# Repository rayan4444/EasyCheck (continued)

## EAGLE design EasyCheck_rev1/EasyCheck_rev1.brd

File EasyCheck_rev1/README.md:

# EasyCheck rev1

This first revision is meant for a purely test basis.
As there are many hardware bugs on this version, the code is just a collection of functions meant to be modified to test a specific feature independently; in preparation for a better version 2 board.

## Hardware Connections
(arduino PIN), Chip Pin: functionality

###### Programming:
- (44) PA30: SWCLK
- (45) PA31: SWDIO
- (28) PA24: USBD_N
- (29) PA25: USBD_P
- NRESET: nRESET

###### Chip Status:
- (26) PA27: Chip 7 status
- (31) PB23: Chip 6 status
- (8) PA06: Chip 5 status
- (9) PA07: Chip 4 status
- (1) PA10: Chip 3 status
- (0) PA11: Chip 2 status
- (2) PA14: Chip 1 status
- (5) PA15: Chip 0 status

###### Chip Serial Number:
- (6) PA20: Serial number 1W

###### User Input:
- (19) PB02: Button 1
- (25) PB03: Button2

###### External ADCs (resistance and chip temperature data):
- (20) PA22 SERCOM 3+5.0: SDA1
- (21) PA23 SERCOM3+5.1: SCL1

###### I2C OLED DISPLAY
- (22) PA12 SERCOM2+4.0: SDA2
- (28) PA13 SERCOM2+4.1: SCL2

###### External DAC (power supply TEC controllers):
- (4) PA08 SERCOM0 + 2.0: SDA3
- (3) PA09 SERCOM 0+ 2.1: SCL3
- (17) PA04: LDAC
- (18) PA05: TEC_EN

###### SPI SD CARD:
- (11) PA16 SERCOM1.0: MOSI
- (13) PA17 SERCOM1.1: SCK
- (10) PA18 SERCOM1.2: /SS
- (12) PA19 SERCOM1.3: MISO
- (30) PB22: Card Detect

###### Device Temperature:
- (7) PA21: 1W Temperature

###### Motor driver TEC input Or Alternative power supply TEC input:
- (15) PB08: PWM0
- (16) PB09: PWM1

###### Alternative power supply TEC input:
- (23) PB10: PWM2
- (24) PB11: PWM3

###### Internal DAC：
- PA02: DAC

## Hardware Errata and fixes

###### Power rail
- 12V to 5V switching regulator: changed from minimum ripple configuration (not working) to minimum cost configuration (see LM5085 datasheet). Still having issues with it output not smooth enough.
- Forgot to connect USB power line to the 5V rail

###### Signals
- I2C1: looks OK
- I2C2: rounded waveform but still functional
- I2C3: does not work. Still uncertain why.
- PWM 2&3 cannot be used with Arduino bootloader
- change 1W resistor to 1.5k for serial number reading
- SD card: remove CS pin pullup

###### Conceptual Errors
- For next version: remove chip status
- Connect every chip serial number to a different pin
- Change I2S screen to SPI screen
- Use Adalogger M0 design for SD card connection
- Change TEC to resistive heater: new driver

## References and Tutorials
###### Programming using OpenOCD and a Raspberry Pi:
- https://learn.adafruit.com/programming-microcontrollers-using-openocd-on-raspberry-pi/overview

###### Assigning SERCOM on SAMD21G:
- https://learn.adafruit.com/using-atsamd21-sercom-to-add-more-spi-i2c-serial-ports/overview

###### Logging data on SD card using RTC for timestamps
- https://github.com/cavemoa/Feather-M0-Adalogger/blob/master/LowPowerLogger/LowPowerLogger.ino

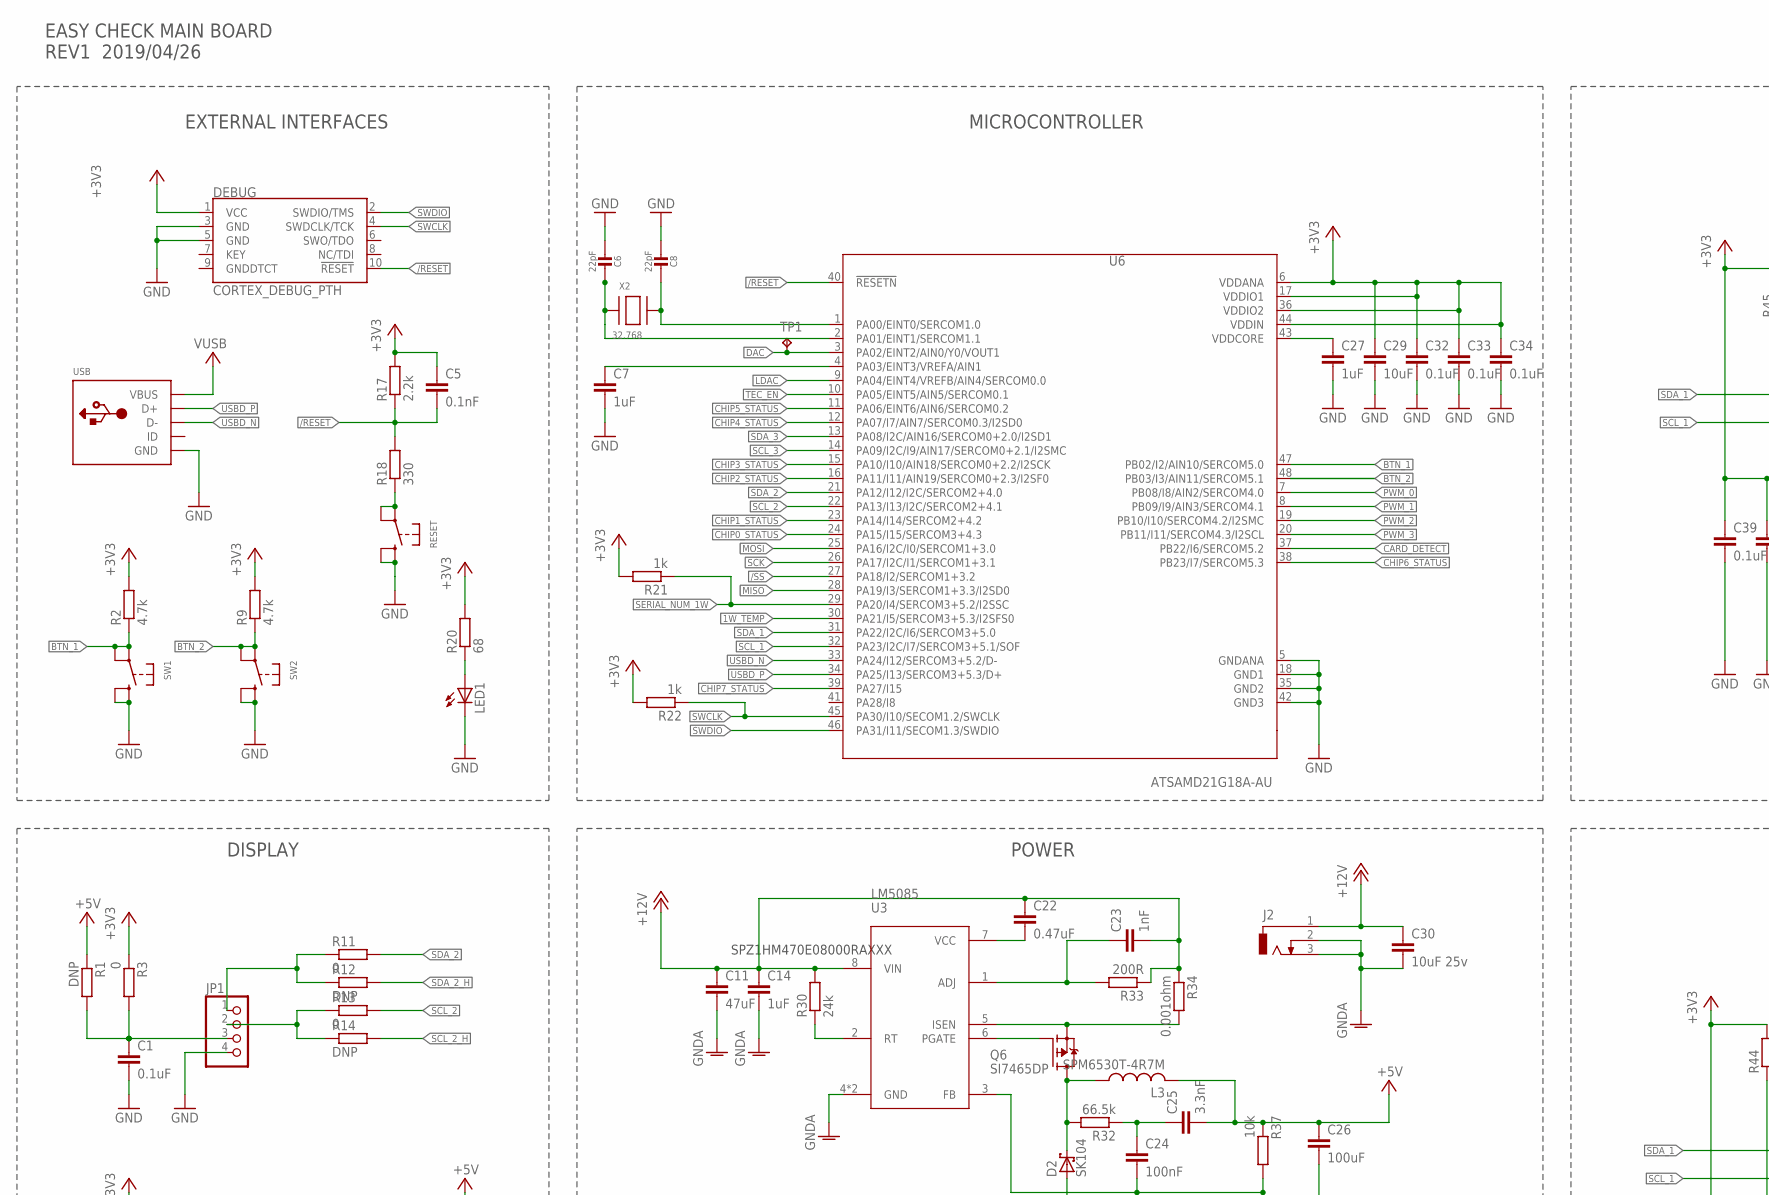
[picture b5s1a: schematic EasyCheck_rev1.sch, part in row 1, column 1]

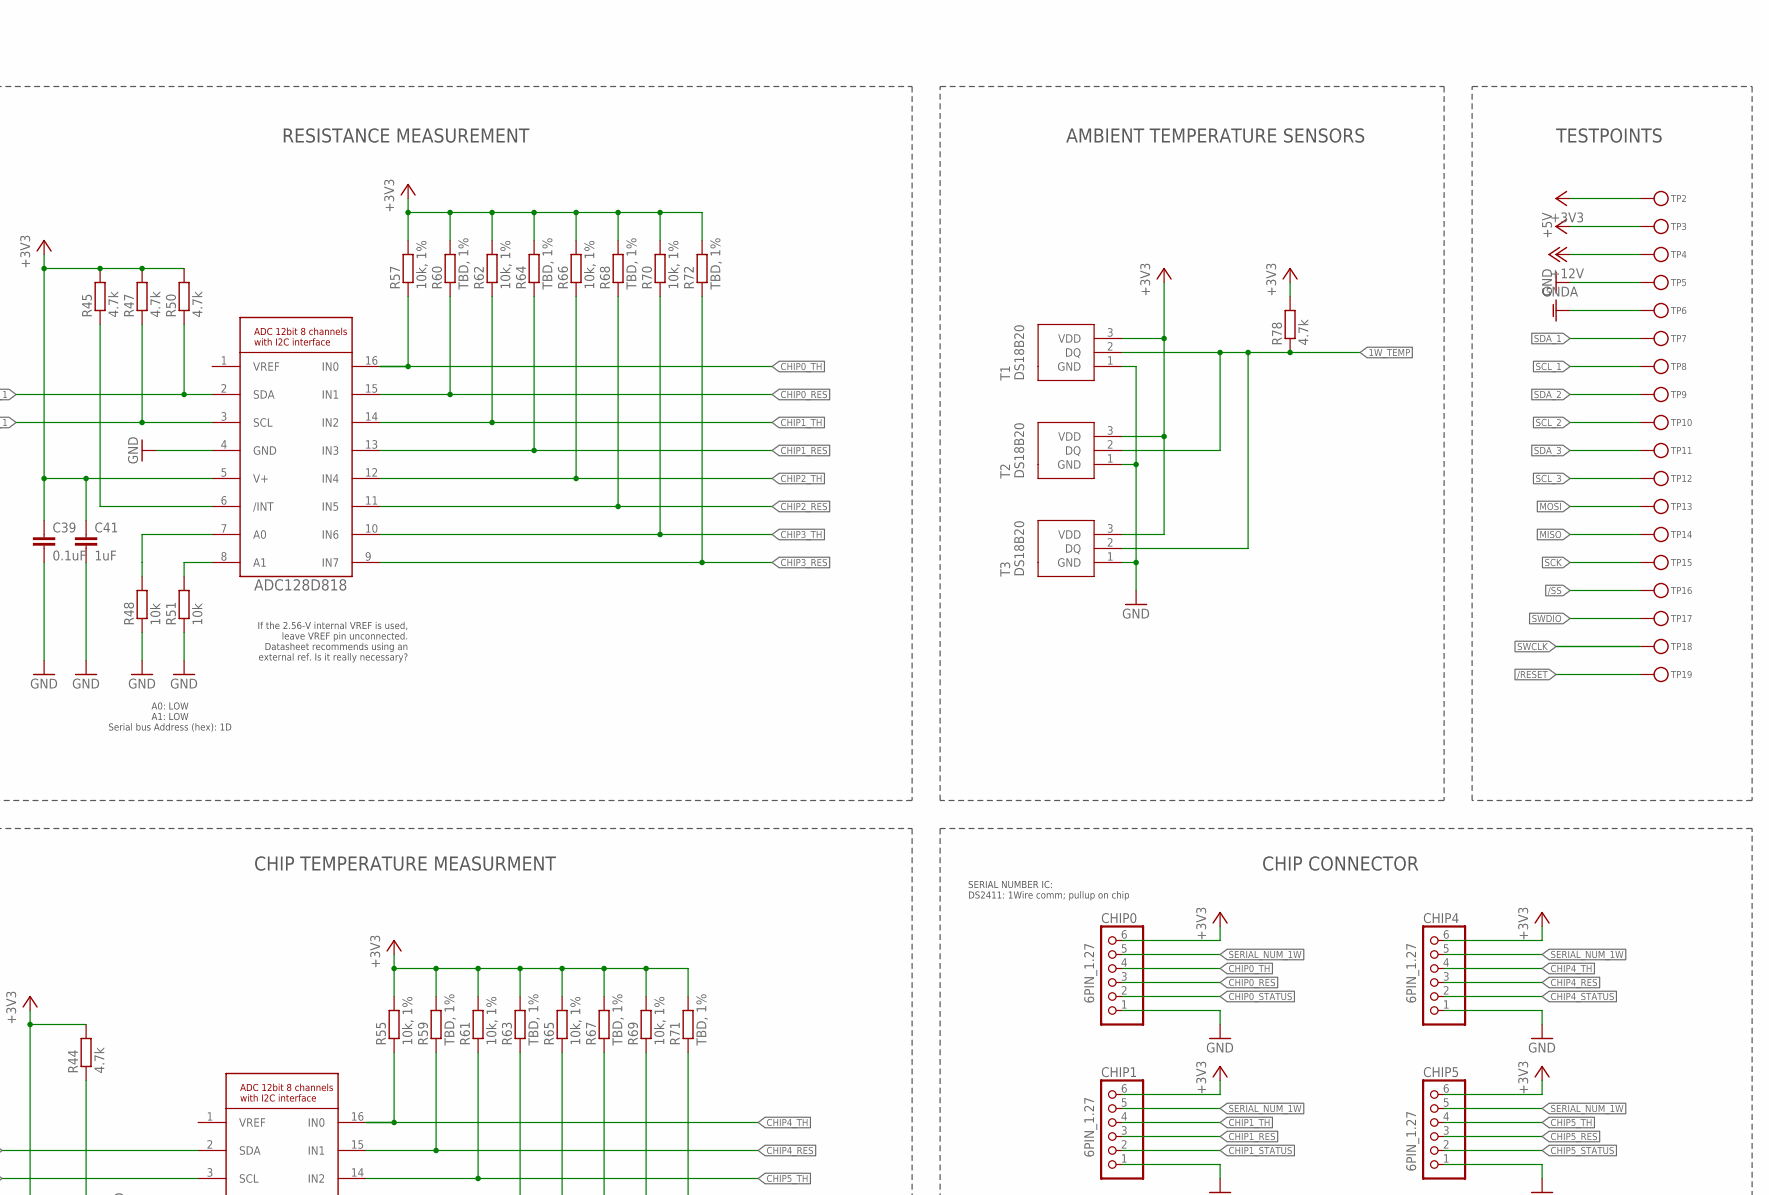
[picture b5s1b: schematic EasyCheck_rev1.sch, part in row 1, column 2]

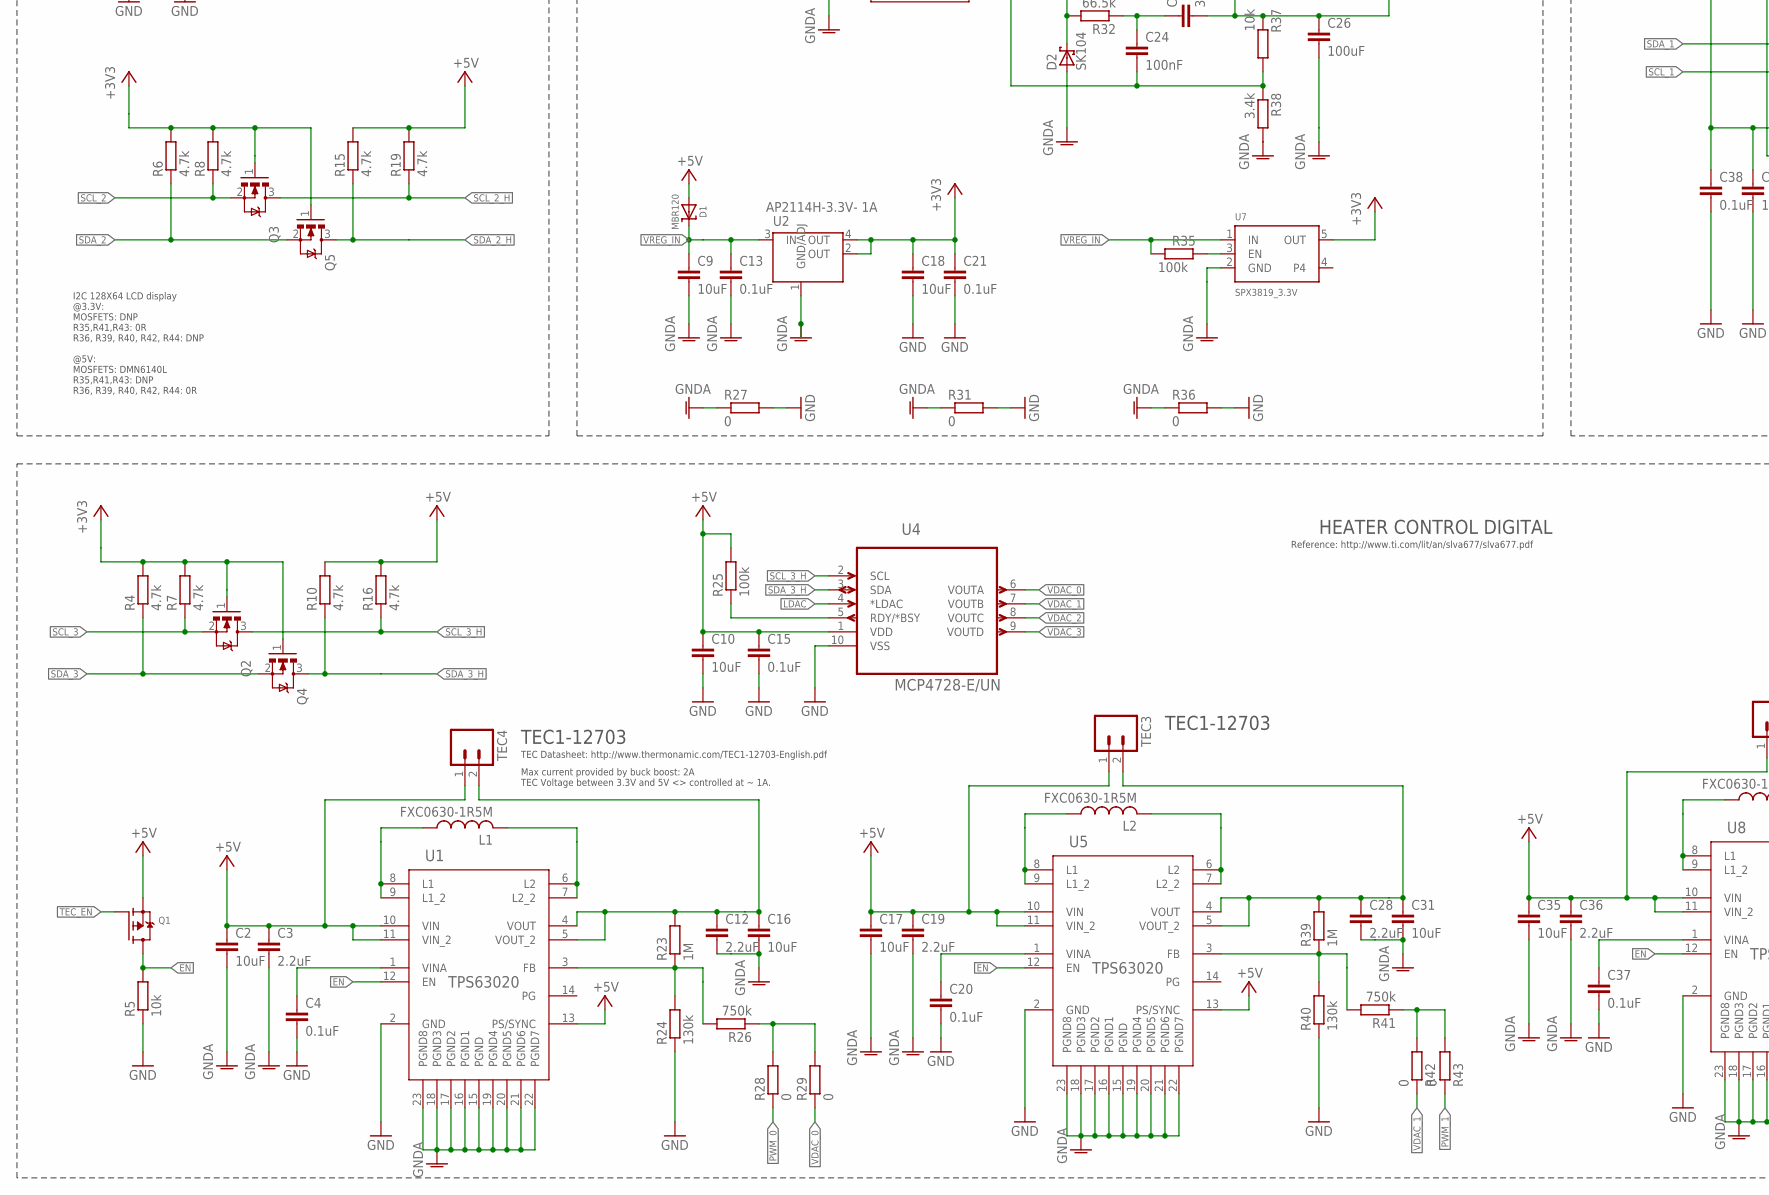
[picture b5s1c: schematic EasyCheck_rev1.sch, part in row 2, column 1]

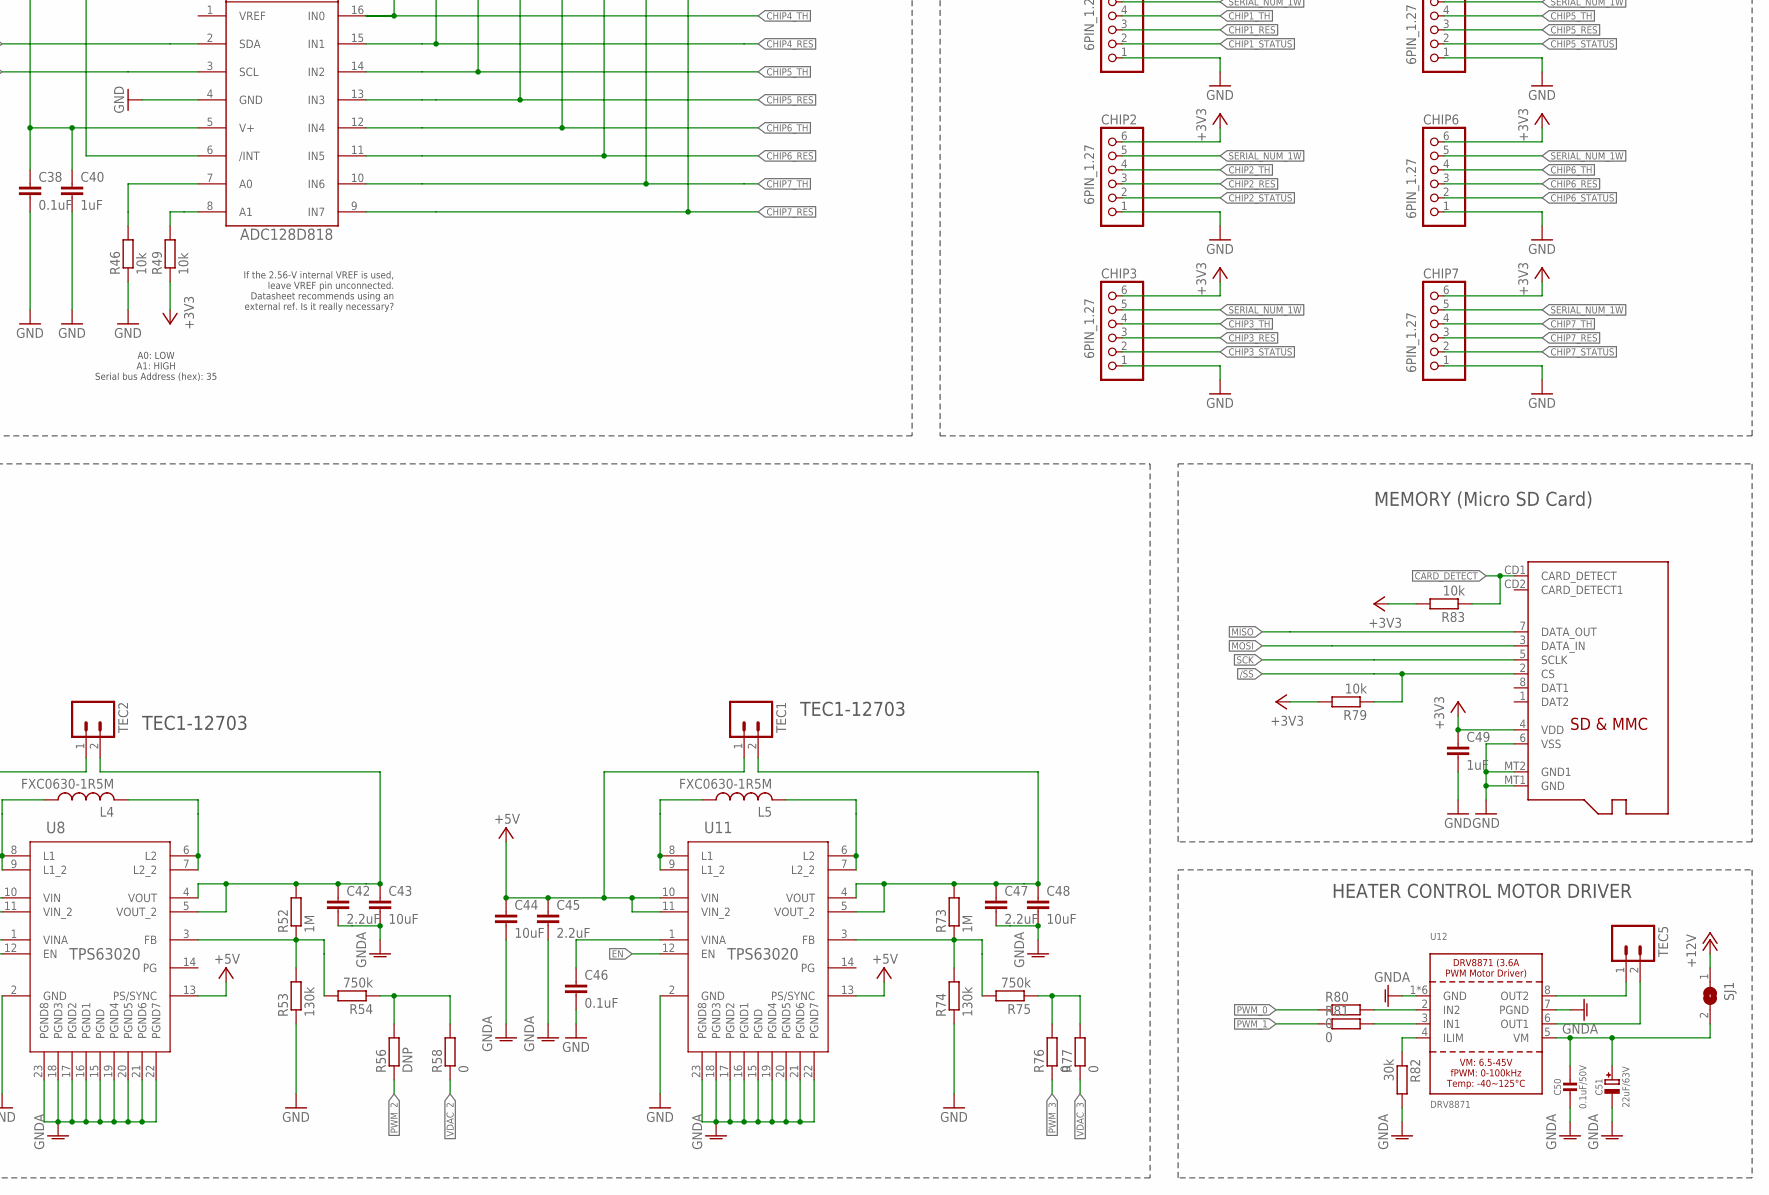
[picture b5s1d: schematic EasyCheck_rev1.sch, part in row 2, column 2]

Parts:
C1, C4, C13, C15, C20, C21, C32, C33, C34, C37, C38, C39, C46: 0.1uF; C0603
C2, C16, C17, C31, C43, C44, C48: 10uF; C0805
C3, C12, C19, C28, C42, C45, C47: 2.2uF; C0805
C5: 0.1nF; C0603
C6, C8: 22pF; 0603-NO
C7, C27, C40, C41, C49: 1uF; C0603
C9, C10, C18, C29, C35: 10uF; C0603
C11: 47uF; C1206
C14: 1uF; C1206
C22: 0.47uF; C1206
C23: 1nF; C0603
C24: 100nF; C0603
C25: 3.3nF; C0603
C26: 100uF; C1206
C30: 10uF 25v; C1206
C36: 2.2uF; C0603
C50: 0.1uF/50V; 0805-NO
C51: 22uF/63V; PANASONIC_D
CHIP0, CHIP1, CHIP2, CHIP3, CHIP4, CHIP5, CHIP6, CHIP7: 6PIN_1.27; 6X1PIN_1.27
D1: MBR120; MICROBUILDER_SOD-123
D2: SK104
DEBUG: CORTEX_DEBUG_PTH; 2X5-PTH-1.27MM
J2: DCJ0303
JP1: PINHD-1X4; 1X04
L1, L2, L4, L5: FXC0630-1R5M; PIS2816
L3: SPM6530T-4R7M
LED1: LEDCHIPLED_0603; CHIPLED_0603
Q1: MICROBUILDER_MOSFET-P; MICROBUILDER_SOT23-R
Q2, Q3, Q4, Q5: DMN6140L; SOT91P240X110-3N
Q6: SI7465DP; SI7465
R1, R12, R14, R56: DNP; R0603
R2, R4, R6, R7, R8, R9, R10, R15, R16, R19, R44, R45, R47, R50, R78: 4.7k; R0603
R3, R11, R13, R27, R28, R29, R31, R36, R42, R43, R58, R76, R77, R80, R81: 0; R0603
R5, R37, R46, R48, R49, R51, R79, R83: 10k; R0603
R17: 2.2k; R0603
R18: 330; R0603
R20: 68; R0603
R21, R22: 1k; R0603
R23, R39, R52, R73: 1M; R0603
R24, R40, R53, R74: 130k; R0603
R25, R35: 100k; R0603
R26, R41, R54, R75: 750k; R0603
R30: 24k; R0603
R32: 66.5k; R0603
R33: 200R; R0603
R34: 0.001ohm; R1206
R38: 3.4k; R0603
R55, R57, R61, R62, R65, R66, R69, R70: 10k, 1%; R0603
R59, R60, R63, R64, R67, R68, R71, R72: TBD, 1%; R0603
R82: 30k; R0603
RESET: MICROBUILDER_SWITCH_TACT_SMT_EVQQ2_SMALL; MICROBUILDER_EVQ-Q2_SMALLER
SD1: MICROSD
SJ1: SJW
SW1, SW2: MICROBUILDER_SWITCH_TACT_SMT_EVQQ2_SMALL; MICROBUILDER_EVQ-Q2_SMALLER
T1, T2, T3: DS18B20; TO92
TEC1, TEC2, TEC3, TEC4, TEC5: SPARKFUN-CONNECTORS_M025MM; SPARKFUN-CONNECTORS_SCREWTERMINAL-5MM-2$1
TP1: TPPAD1-17; P1-17
TP2, TP3, TP4, TP5, TP6, TP7, TP8, TP9, TP10, TP11, TP12, TP13, TP14, TP15, TP16, TP17, TP18, TP19: MICROBUILDER_TESTPOINTROUND1.5MM; MICROBUILDER_TESTPOINT_ROUND_1.5MM
U1, U5, U8, U11: TPS63020; QFN14-3X4MM
U2: AP2114H-3.3V- 1A; GEN_COMP_SOT223
U3: LM5085
U4: MCP4728-E/UN; SOP50P490X110-10N
U6: ATSAMD21G18A-AU; QFP50P900X900X120-48N
U7: SPX3819_3.3V; MICROBUILDER_SOT23-5
U9, U10: LMD128D818; ADC128D818
U12: DRV8871; HSOP8
USB: MICROBUILDER_USB_MICRO_20329_V2; MICROBUILDER_4UCONN_20329_V2
X2: 32.768; XTAL3215

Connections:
1W_TEMP: R78.1, T1.2 (DQ), T2.2 (DQ), T3.2 (DQ), U6.30 (PA21/I5/SERCOM3+5.3/I2SFS0)
+3V3: C5.1, C18.1, C21.1, C29.1, C32.1, C33.1, C34.1, C38.1, C39.1, C40.1, C41.1, C49.1, CHIP0.6, CHIP1.6, CHIP2.6, CHIP3.6, CHIP4.6, CHIP5.6, CHIP6.6, CHIP7.6, DEBUG.1 (VCC), Q2.1, Q3.1, Q4.1, Q5.1, R2.2, R3.1, R4.2, R6.2, R7.2, R8.2, R9.2, R17.2, R20.2, R21.2, R22.2, R44.2, R45.2, R47.2, R49.1, R50.2, R55.2, R57.2, R59.2, R60.2, R61.2, R62.2, R63.2, R64.2, R65.2, R66.2, R67.2, R68.2, R69.2, R70.2, R71.2, R72.2, R78.2, R79.2, R83.2, SD1.4 (VDD), T1.3 (VDD), T2.3 (VDD), T3.3 (VDD), TP2.P$1, U2.2 (OUT), U2.4 (OUT), U6.6 (VDDANA), U6.17 (VDDIO1), U6.36 (VDDIO2), U6.44 (VDDIN), U7.5 (OUT), U9.5 (V+), U10.5 (V+)
+5V: C2.1, C3.1, C10.1, C15.1, C17.1, C19.1, C25.2, C26.1, C35.1, C36.1, C44.1, C45.1, D1.A, L3.2, Q1.2 (S), R1.1, R10.2, R15.2, R16.2, R19.2, R25.2, R37.1, TEC1.1, TEC2.1, TEC3.1, TEC4.1, TP3.P$1, U1.10 (VIN), U1.11 (VIN_2), U1.13 (PS/SYNC), U4.1 (VDD), U5.10 (VIN), U5.11 (VIN_2), U5.13 (PS/SYNC), U8.10 (VIN), U8.11 (VIN_2), U8.13 (PS/SYNC), U11.10 (VIN), U11.11 (VIN_2), U11.13 (PS/SYNC)
+12V: C11.1, C14.1, C22.1, C23.2, C30.1, J2.1, R30.2, R33.1, R34.1, SJ1.1, TP4.P$1, U3.8 (VIN)
/RESET: C5.2, DEBUG.10 (!RESET), R17.1, R18.2, TP19.P$1, U6.40 (!RESETN)
/SS: R79.1, SD1.2 (CS), TP16.P$1, U6.27 (PA18/I2/SERCOM1+3.2)
BTN_1: R2.1, SW1.A, SW1.A' (P1), U6.47 (PB02/I2/AIN10/SERCOM5.0)
BTN_2: R9.1, SW2.A, SW2.A' (P1), U6.48 (PB03/I3/AIN11/SERCOM5.1)
CARD_DETECT: R83.1, SD1.CD1 (CARD_DETECT), U6.37 (PB22/I6/SERCOM5.2)
CHIP0_RES: CHIP0.3, R60.1, U10.15 (IN1)
CHIP0_STATUS: CHIP0.2, U6.24 (PA15/I15/SERCOM3+4.3)
CHIP0_TH: CHIP0.4, R57.1, U10.16 (IN0)
CHIP1_RES: CHIP1.3, R64.1, U10.13 (IN3)
CHIP1_STATUS: CHIP1.2, U6.23 (PA14/I14/SERCOM2+4.2)
CHIP1_TH: CHIP1.4, R62.1, U10.14 (IN2)
CHIP2_RES: CHIP2.3, R68.1, U10.11 (IN5)
CHIP2_STATUS: CHIP2.2, U6.16 (PA11/I11/AIN19/SERCOM0+2.3/I2SF0)
CHIP2_TH: CHIP2.4, R66.1, U10.12 (IN4)
CHIP3_RES: CHIP3.3, R72.1, U10.9 (IN7)
CHIP3_STATUS: CHIP3.2, U6.15 (PA10/I10/AIN18/SERCOM0+2.2/I2SCK)
CHIP3_TH: CHIP3.4, R70.1, U10.10 (IN6)
CHIP4_RES: CHIP4.3, R59.1, U9.15 (IN1)
CHIP4_STATUS: CHIP4.2, U6.12 (PA07/I7/AIN7/SERCOM0.3/I2SD0)
CHIP4_TH: CHIP4.4, R55.1, U9.16 (IN0)
CHIP5_RES: CHIP5.3, R63.1, U9.13 (IN3)
CHIP5_STATUS: CHIP5.2, U6.11 (PA06/EINT6/AIN6/SERCOM0.2)
CHIP5_TH: CHIP5.4, R61.1, U9.14 (IN2)
CHIP6_RES: CHIP6.3, R67.1, U9.11 (IN5)
CHIP6_STATUS: CHIP6.2, U6.38 (PB23/I7/SERCOM5.3)
CHIP6_TH: CHIP6.4, R65.1, U9.12 (IN4)
CHIP7_RES: CHIP7.3, R71.1, U9.9 (IN7)
CHIP7_STATUS: CHIP7.2, U6.39 (PA27/I15)
CHIP7_TH: CHIP7.4, R69.1, U9.10 (IN6)
DAC: TP1.TP, U6.3 (PA02/EINT2/AIN0/Y0/VOUT1)
EN: Q1.3 (D), R5.2, U1.12 (EN), U5.12 (EN), U8.12 (EN), U11.12 (EN)
GND: C1.2, C4.2, C6.2, C7.2, C8.2, C10.2, C15.2, C18.2, C20.2, C21.2, C27.2, C29.2, C32.2, C33.2, C34.2, C37.2, C38.2, C39.2, C40.2, C41.2, C46.2, C49.2, CHIP0.1, CHIP1.1, CHIP2.1, CHIP3.1, CHIP4.1, CHIP5.1, CHIP6.1, CHIP7.1, DEBUG.3 (GND), DEBUG.5 (GND), JP1.4, LED1.C, R5.1, R24.1, R27.2, R31.2, R36.2, R40.1, R46.1, R48.1, R51.1, R53.1, R74.1, RESET.B (S), RESET.B' (S1), SD1.6 (VSS), SD1.MT1 (GND), SD1.MT2 (GND1), SW1.B (S), SW1.B' (S1), SW2.B (S), SW2.B' (S1), T1.1 (GND), T2.1 (GND), T3.1 (GND), TP5.P$1, U1.2 (GND), U4.10 (VSS), U5.2 (GND), U6.5 (GNDANA), U6.18 (GND1), U6.35 (GND2), U6.42 (GND3), U8.2 (GND), U9.4 (GND), U10.4 (GND), U11.2 (GND), USB.BASE@1 (GND), USB.BASE@2 (GND), USB.GND, USB.SPRT@1 (GND), USB.SPRT@2 (GND), USB.SPRT@3 (GND), USB.SPRT@4 (GND)
GNDA: C2.2, C3.2, C9.2, C11.2, C12.2, C13.2, C14.2, C16.2, C17.2, C19.2, C26.2, C28.2, C30.2, C31.2, C35.2, C36.2, C42.2, C43.2, C44.2, C45.2, C47.2, C48.2, C50.2, C51.-, D2.1 (A), J2.2, J2.3, R27.1, R31.1, R36.1, R38.2, R82.2, TP6.P$1, U1.15 (PGND), U1.16 (PGND1), U1.17 (PGND2), U1.18 (PGND3), U1.19 (PGND4), U1.20 (PGND5), U1.21 (PGND6), U1.22 (PGND7), U1.23 (PGND8), U2.1 (GND/ADJ), U3.4 (GND), U3.9 (GND), U5.15 (PGND), U5.16 (PGND1), U5.17 (PGND2), U5.18 (PGND3), U5.19 (PGND4), U5.20 (PGND5), U5.21 (PGND6), U5.22 (PGND7), U5.23 (PGND8), U7.2 (GND), U8.15 (PGND), U8.16 (PGND1), U8.17 (PGND2), U8.18 (PGND3), U8.19 (PGND4), U8.20 (PGND5), U8.21 (PGND6), U8.22 (PGND7), U8.23 (PGND8), U11.15 (PGND), U11.16 (PGND1), U11.17 (PGND2), U11.18 (PGND3), U11.19 (PGND4), U11.20 (PGND5), U11.21 (PGND6), U11.22 (PGND7), U11.23 (PGND8), U12.1 (GND), U12.7 (PGND), U12.GND, U12.P$1 (GND), U12.P$2 (GND), U12.P$3 (GND), U12.P$4 (GND)
LDAC: U4.4 (*LDAC), U6.9 (PA04/EINT4/VREFB/AIN4/SERCOM0.0)
MISO: SD1.7 (DATA_OUT), TP14.P$1, U6.28 (PA19/I3/SERCOM1+3.3/I2SD0)
MOSI: SD1.3 (DATA_IN), TP13.P$1, U6.25 (PA16/I2C/I0/SERCOM1+3.0)
unnamed: R45.1, U10.6 (/INT)
unnamed: R44.1, U9.6 (/INT)
unnamed: R48.2, U10.7 (A0)
unnamed: R51.2, U10.8 (A1)
unnamed: R46.2, U9.7 (A0)
unnamed: R49.2, U9.8 (A1)
unnamed: R18.1, RESET.A, RESET.A' (P1)
unnamed: R35.2, U7.3 (EN)
unnamed: JP1.1, R11.1, R12.1
unnamed: C6.1, U6.2 (PA01/EINT1/SERCOM1.1), X2.P$1
unnamed: C8.1, U6.1 (PA00/EINT0/SERCOM1.0), X2.P$2
unnamed: C7.1, U6.4 (PA03/EINT3/VREFA/AIN1)
unnamed: C27.1, U6.43 (VDDCORE)
unnamed: LED1.A, R20.1
unnamed: JP1.2, R13.1, R14.1
unnamed: R26.1, R28.2, R29.2
unnamed: R23.1, R24.2, R26.2, U1.3 (FB)
unnamed: C4.1, U1.1 (VINA)
unnamed: L1.1, U1.8 (L1), U1.9 (L1_2)
unnamed: C12.1, C16.1, R23.2, TEC4.2, U1.4 (VOUT), U1.5 (VOUT_2)
unnamed: L1.2, U1.6 (L2), U1.7 (L2_2)
unnamed: R41.1, R42.2, R43.2
unnamed: C20.1, U5.1 (VINA)
unnamed: R30.1, U3.2 (RT)
unnamed: R39.1, R40.2, R41.2, U5.3 (FB)
unnamed: C28.1, C31.1, R39.2, TEC3.2, U5.4 (VOUT), U5.5 (VOUT_2)
unnamed: L2.1, U5.8 (L1), U5.9 (L1_2)
unnamed: L2.2, U5.6 (L2), U5.7 (L2_2)
unnamed: R25.1, U4.5 (RDY/*BSY)
unnamed: R54.1, R56.2, R58.2
unnamed: C37.1, U8.1 (VINA)
unnamed: R52.1, R53.2, R54.2, U8.3 (FB)
unnamed: C42.1, C43.1, R52.2, TEC2.2, U8.4 (VOUT), U8.5 (VOUT_2)
unnamed: L4.1, U8.8 (L1), U8.9 (L1_2)
unnamed: L4.2, U8.6 (L2), U8.7 (L2_2)
unnamed: Q6.1 (S), Q6.2 (S), Q6.3 (S), R34.2, U3.5 (ISEN)
unnamed: R75.1, R76.2, R77.2
unnamed: C23.1, R33.2, U3.1 (ADJ)
unnamed: C24.1, C25.1, R32.1
unnamed: C24.2, R37.2, R38.1, U3.3 (FB)
unnamed: C46.1, U11.1 (VINA)
unnamed: R73.1, R74.2, R75.2, U11.3 (FB)
unnamed: C22.2, U3.7 (VCC)
unnamed: C47.1, C48.1, R73.2, TEC1.2, U11.4 (VOUT), U11.5 (VOUT_2)
unnamed: L5.1, U11.8 (L1), U11.9 (L1_2)
unnamed: L5.2, U11.6 (L2), U11.7 (L2_2)
unnamed: D2.2 (C), L3.1, Q6.5 (D), Q6.6 (D), Q6.7 (D), Q6.8 (D), Q6.9 (D), R32.2
unnamed: Q6.4 (G), U3.6 (PGATE)
unnamed: R82.1, U12.4 (ILIM)
unnamed: R80.2, U12.2 (IN2)
unnamed: R81.2, U12.3 (IN1)
unnamed: C50.1, C51.+, SJ1.2, U12.5 (VM)
OUT1: TEC5.2, U12.6 (OUT1)
OUT2: TEC5.1, U12.8 (OUT2)
PWM_0: R28.1, R80.1, U6.7 (PB08/I8/AIN2/SERCOM4.0)
PWM_1: R43.1, R81.1, U6.8 (PB09/I9/AIN3/SERCOM4.1)
PWM_2: R56.1, U6.19 (PB10/I10/SERCOM4.2/I2SMC)
PWM_3: R76.1, U6.20 (PB11/I11/SERCOM4.3/I2SCL)
SCK: SD1.5 (SCLK), TP15.P$1, U6.26 (PA17/I2C/I1/SERCOM1+3.1)
SCL_1: R47.1, TP8.P$1, U6.32 (PA23/I2C/I7/SERCOM3+5.1/SOF), U9.3 (SCL), U10.3 (SCL)
SCL_2: Q3.2, R8.1, R13.2, TP10.P$1, U6.22 (PA13/I13/I2C/SERCOM2+4.1)
SCL_2_H: Q3.3, R14.2, R19.1
SCL_3: Q2.2, R7.1, TP12.P$1, U6.14 (PA09/I2C/I9/AIN17/SERCOM0+2.1/I2SMC)
SCL_3_H: Q2.3, R16.1, U4.2 (SCL)
SDA_1: R50.1, TP7.P$1, U6.31 (PA22/I2C/I6/SERCOM3+5.0), U9.2 (SDA), U10.2 (SDA)
SDA_2: Q5.2, R6.1, R11.2, TP9.P$1, U6.21 (PA12/I12/I2C/SERCOM2+4.0)
SDA_2_H: Q5.3, R12.2, R15.1
SDA_3: Q4.2, R4.1, TP11.P$1, U6.13 (PA08/I2C/AIN16/SERCOM0+2.0/I2SD1)
SDA_3_H: Q4.3, R10.1, U4.3 (SDA)
SERIAL_NUM_1W: CHIP0.5, CHIP1.5, CHIP2.5, CHIP3.5, CHIP4.5, CHIP5.5, CHIP6.5, CHIP7.5, R21.1, U6.29 (PA20/I4/SERCOM3+5.2/I2SSC)
SWCLK: DEBUG.4 (SWDCLK/TCK), R22.1, TP18.P$1, U6.45 (PA30/I10/SECOM1.2/SWCLK)
SWDIO: DEBUG.2 (SWDIO/TMS), TP17.P$1, U6.46 (PA31/I11/SECOM1.3/SWDIO)
TEC_EN: Q1.1 (G), U6.10 (PA05/EINT5/AIN5/SERCOM0.1)
USBD_N: U6.33 (PA24/I12/SERCOM3+5.2/D-), USB.D-
USBD_P: U6.34 (PA25/I13/SERCOM3+5.3/D+), USB.D+
VCC: C1.1, JP1.3, R1.2, R3.2
VDAC_0: R29.1, U4.6 (VOUTA)
VDAC_1: R42.1, U4.7 (VOUTB)
VDAC_2: R58.1, U4.8 (VOUTC)
VDAC_3: R77.1, U4.9 (VOUTD)
VREG_IN: C9.1, C13.1, D1.C, R35.1, U2.3 (IN), U7.1 (IN)

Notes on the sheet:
EASY CHECK MAIN BOARD REV1 2019/04/26
CHIP CONNECTOR
DISPLAY
EXTERNAL INTERFACES
HEATER CONTROL DIGITAL
AMBIENT TEMPERATURE SENSORS
RESISTANCE MEASUREMENT
POWER
SERIAL NUMBER IC: DS2411: 1Wire comm; pullup on chip
CHIP TEMPERATURE MEASURMENT
If the 2.56-V internal VREF is used, leave VREF pin unconnected. Datasheet recommends using an external ref. Is it really necessary?
A0: LOW A1: LOW Serial bus Address (hex): 1D
A0: LOW A1: HIGH Serial bus Address (hex): 35
MICROCONTROLLER
I2C 128X64 LCD display @3.3V: MOSFETS: DNP R35,R41,R43: 0R R36, R39, R40, R42, R44: DNP @5V: MOSFETS: DMN6140L R35,R41,R43: DNP R36, R39, R40, R42, R44: 0R
TESTPOINTS
MEMORY (Micro SD Card)
Reference: http://www.ti.com/lit/an/slva677/slva677.pdf
TEC1-12703
TEC Datasheet: http://www.thermonamic.com/TEC1-12703-English.pdf
Max current provided by buck boost: 2A TEC Voltage between 3.3V and 5V <> controlled at ~ 1A.
HEATER CONTROL MOTOR DRIVER
SPZ1HM470E08000RAXXX

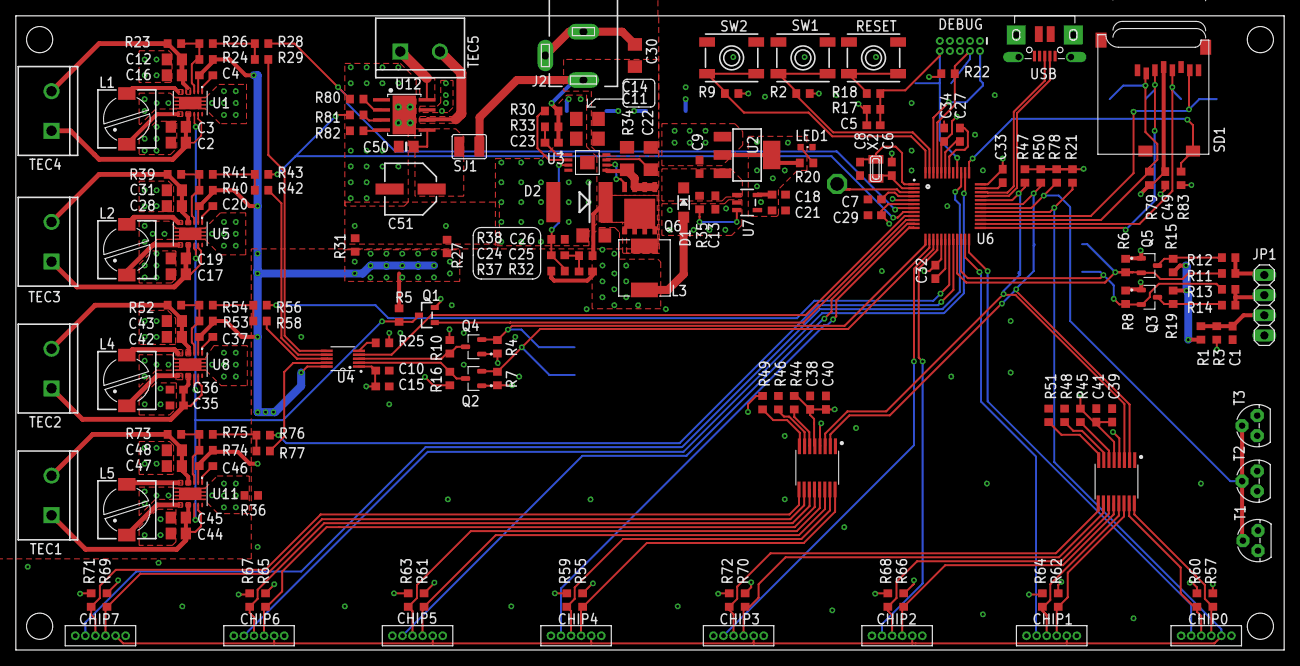
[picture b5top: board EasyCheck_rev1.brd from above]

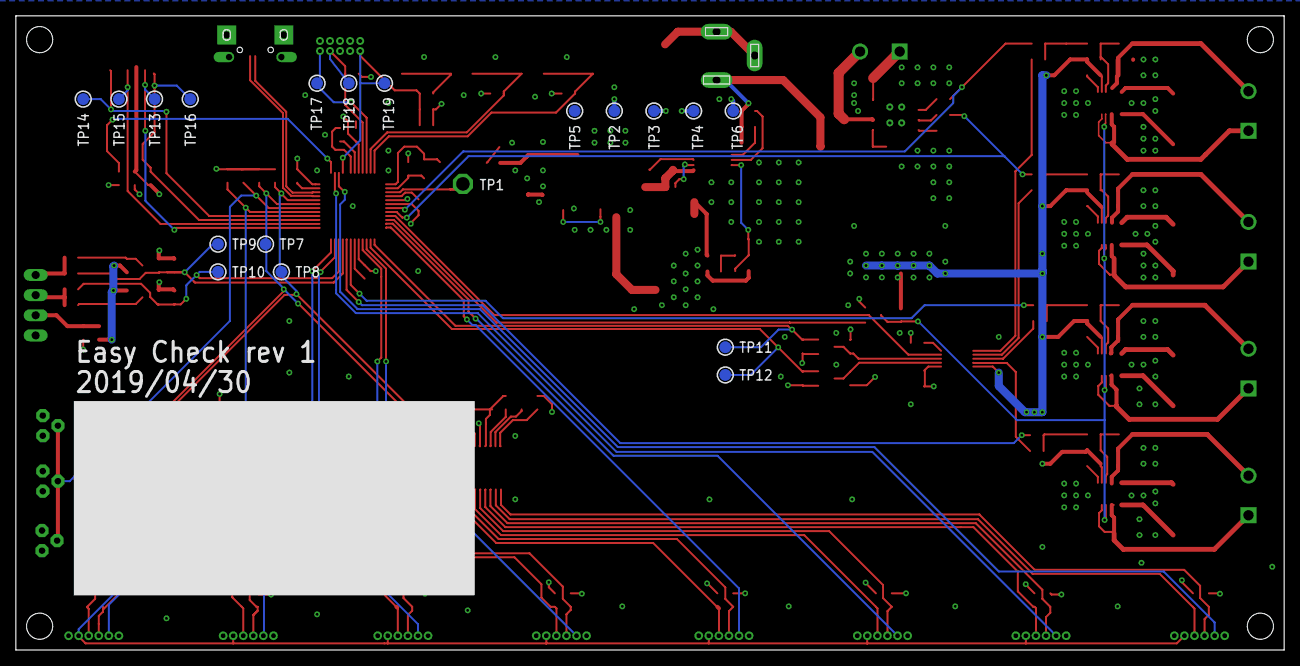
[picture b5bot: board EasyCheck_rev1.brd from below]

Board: 4 copper layers, 160.0 x 80.0 mm, 205 parts (19 on the bottom side), 121 nets.

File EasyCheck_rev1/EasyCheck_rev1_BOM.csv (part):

BOM EASY CHECK REV1 - CHIP,,1 batch has 8 chips ,,,,,,,,,,,,,,,,,
#,Parts,Value,Qty,Device,Package,Description,MPN, Unit Price  ,Total Price,Purchase Link,,,,,,,,,
1,"R2,R3",100R,16,R0402,R0402,Resistor,, ¥0.002 , ¥0.03 ,https://item.szlcsc.com/107447.html,1,,,,,,,,
2,R4,1k,8,R0402,R0402,Resistor,, ¥0.003 , ¥0.02 ,https://item.szlcsc.com/175251.html,1,,,,,,,,
3,U1,ERT-J1VR103J,8,NTC_SMD,R0603,NTC thermistor,ERT-J1VR103J, ¥1.080 , ¥8.64 ,https://item.szlcsc.com/164385.html,1,,,,,,,,
4,U2,Easycheck_chip,8,Easycheck_chip,5mmx2mm,Easy Check sensing paper strip ,, ¥-   , ¥-   ,N.A.,,,,,,,,,
5,U3,DS2411,8,DS2411,SOT23,1 Wire Serial Number IC,DS2411R+T&R, ¥3.900 , ¥31.20 ,https://item.szlcsc.com/16300.html,1,,,,,,,,
6,LED1,RED,8,LEDCHIPLED_0603,CHIPLED_0603,LED,, ¥0.050 , ¥0.40 ,https://detail.tmall.com/item.htm?id=41231498462,,,,,,,,,
7,LED2,GREEN,8,LEDCHIPLED_0603,CHIPLED_0603,LED,, ¥0.050 , ¥0.40 ,https://detail.tmall.com/item.htm?id=41231498462,,,,,,,,,
8,J1,6PIN_1.27_MALE,8,6PIN_1.27_MALE,6PIN_1.27,6x1 1.27mm pitch Male pin header,, ¥1.000 , ¥8.00 ,https://detail.tmall.com/item.htm?id=44143324234,,,,,,,,,
Total,,,,,,,,, ¥48.70 ,,,,,,,,,,
,,,,,,,,,,,,,,,,,,,
BOM EASY CHECK REV1 - Main Board,,,,,,,,,,,,,,,,,,,
,,,,,,,,,,,,,,,,,,,
#,Parts,Value,Qty,Device,Package,Description,MPN, Unit Price  ,Total Price,Purchase Link,,,,,,,,,
,"R3, R11, R13, R27, R28, R29, R31, R36, R42, R43, R56, R58, R76, R77, R80, R81",0R,16,R0603,R0603,Resistor,, ¥0.006 , ¥0.10 ,https://item.szlcsc.com/21903.html,1,,,,,,,,
,R34,0.001ohm,1,R1206,R1206,Resistor,, ¥0.500 , ¥0.50 ,https://item.szlcsc.com/165971.html,1,,,,,,,,
,R20,68R,1,R0603,R0603,Resistor,, ¥0.017 , ¥0.02 ,https://item.szlcsc.com/188933.html,1,,,,,,,,
,R33,200R,1,R0603,R0603,Resistor,, ¥0.016 , ¥0.02 ,https://item.szlcsc.com/339618.html,1,,,,,,,,
,R18,330R,1,R0603,R0603,Resistor,, ¥0.016 , ¥0.02 ,https://item.szlcsc.com/339635.html,1,,,,,,,,
,"R21, R22",1k,2,R0603,R0603,Resistor,, ¥0.006 , ¥0.01 ,https://item.szlcsc.com/21904.html,1,,,,,,,,
,R17,2.2k,1,R0603,R0603,Resistor,, ¥0.006 , ¥0.01 ,https://item.szlcsc.com/4597.html,1,,,,,,,,
, ,3.4k,1,R0603,R0603,Resistor,, ¥0.008 , ¥0.01 ,https://item.szlcsc.com/23724.html,1,,,,,,,,
,"R2, R4, R6, R7, R8, R9, R10, R15, R16, R19, R44, R45, R47, R50, R78",4.7k,15,R0603,R0603,Resistor,, ¥0.008 , ¥0.12 ,https://item.szlcsc.com/23889.html,1,,,,,,,,
,"R5, R37, R46, R48, R49, R51, R79, R83",10k,8,R0603,R0603,Resistor,, ¥0.006 , ¥0.05 ,https://item.szlcsc.com/26547.html,1,,,,,,,,
,"R55, R57, R61, R62, R65, R66, R69, R70","10k, 0.1%",8,R0603,R0603,Resistor,, ¥0.179 , ¥1.43 ,https://item.szlcsc.com/96405.html,1,,,,,,,,
,R30,24k,1,R0603,R0603,Resistor,, ¥0.006 , ¥0.01 ,https://item.szlcsc.com/263994.html,1,,,,,,,,
,R82,30k,1,R0603,R0603,Resistor,, ¥0.006 , ¥0.01 ,https://item.szlcsc.com/23711.html,1,,,,,,,,
,R32,66.5k,1,R0603,R0603,Resistor,, ¥0.007 , ¥0.01 ,https://item.szlcsc.com/23952.html,1,,,,,,,,
,"R25, R35",100k,2,R0603,R0603,Resistor,, ¥0.006 , ¥0.01 ,https://item.szlcsc.com/26546.html,1,,,,,,,,
,"R24, R40, R53, R74",130k,4,R0603,R0603,Resistor,, ¥0.006 , ¥0.02 ,https://item.szlcsc.com/279171.html,1,,,,,,,,
,"R26, R41, R54, R75",750k,4,R0603,R0603,Resistor,, ¥0.005 , ¥0.02 ,https://item.szlcsc.com/26748.html,1,,,,,,,,
,"R23, R39, R52, R73",1M,4,R0603,R0603,Resistor,, ¥0.006 , ¥0.02 ,https://item.szlcsc.com/175251.html,1,,,,,,,,
,"R59, R60, R63, R64, R67, R68, R71, R72","TBD, 1%",8,R0603,R0603,Resistor,,, ¥-   ,N.A.,,,,,,,,,
,"R1, R12, R14",DNP,3,R0603,R0603,Resistor,,, ¥-   ,N.A.,,,,,,,,,
,C5,100pF,1,C0603,C0603,Ceramic Capacitor,, ¥0.014 , ¥0.01 ,https://item.szlcsc.com/251398.html,1,,,,,,,,
,"C1, C4, C13, C15, C20, C21, C24, C32, C33, C34, C37, C38, C39, C46",0.1uF,14,C0603,C0603,Ceramic Capacitor,, ¥0.016 , ¥0.22 ,https://item.szlcsc.com/43989.html,1,,,,,,,,
,C23,1nF,1,C0603,C0603,Ceramic Capacitor,, ¥0.009 , ¥0.01 ,https://item.szlcsc.com/251401.html,1,,,,,,,,
,"C7, C27, C40, C41, C49",1uF,5,C0603,C0603,Ceramic Capacitor,, ¥0.050 , ¥0.25 ,https://item.szlcsc.com/16531.html,1,,,,,,,,
,f,10uF,5,C0603,C0603,Ceramic Capacitor,, ¥0.140 , ¥0.70 ,https://item.szlcsc.com/109559.html,1,,,,,,,,
,C36,2.2uF,1,C0603,C0603,Ceramic Capacitor,, ¥0.060 , ¥0.06 ,https://item.szlcsc.com/24366.html,1,,,,,,,,
,"C6, C8",22pF,2,C0603,C0603,Ceramic Capacitor,, ¥0.020 , ¥0.04 ,https://item.szlcsc.com/292465.html,11,,,,,,,,
,C25,3.3nF,1,C0603,C0603,Ceramic Capacitor,, ¥0.020 , ¥0.02 ,https://item.szlcsc.com/93394.html,1,,,,,,,,
,C50,0.1uF/50V,1,C0805,C0805,Ceramic Capacitor,, ¥0.030 , ¥0.03 ,https://item.szlcsc.com/268703.html,1,,,,,,,,
,"C3, C12, C19, C28, C42, C45, C47",2.2uF,7,C0805,C0805,Ceramic Capacitor,, ¥0.100 , ¥0.70 ,https://item.szlcsc.com/89172.html,1,,,,,,,,
,"C2, C16, C17, C31, C43, C44, C48",10uF,7,C0805,C0805,Ceramic Capacitor,, ¥0.120 , ¥0.84 ,https://item.szlcsc.com/16532.html,1,,,,,,,,
,C14,1uF,1,C1206,C1206,Ceramic Capacitor,, ¥0.140 , ¥0.14 ,https://item.szlcsc.com/349429.html,1,,,,,,,,
,C22,0.47uF,1,C1206,C1206,Ceramic Capacitor,, ¥0.100 , ¥0.10 ,https://item.szlcsc.com/354881.html,1,,,,,,,,
,C30,10uF 25v,1,C1206,C1206,Ceramic Capacitor,, ¥0.310 , ¥0.31 ,https://item.szlcsc.com/10337.html,1,,,,,,,,
,C11,47uF,1,C1206,C1206,Ceramic Capacitor,, ¥0.700 , ¥0.70 ,https://item.szlcsc.com/95232.html,1,,,,,,,,
,C26,100uF,1,C1206,C1206,Ceramic Capacitor,, ¥1.390 , ¥1.39 ,https://item.szlcsc.com/15681.html,1,,,,,,,,
,C51,22uF/63V,1,CAP_ELECTROLYTICPANASONIC_D,PANASONIC_D,Electrolytic Capacitor,, ¥0.600 , ¥0.60 ,https://item.szlcsc.com/245610.html,1,,,,,,,,
,"L1, L2, L4, L5",1.5uH ±20% 9A,4,FXC0630-1R5M,PIS2816,Inductor,FXC0630-1R5M, ¥0.640 , ¥2.56 ,https://item.szlcsc.com/209167.html,1,,,,,,,,
,L3,4.7uH±20% ,1,SPM6530T-4R7M,SPM6530T-4R7M,Inductor,SPM6530T-4R7M, ¥0.920 , ¥0.92 ,https://item.szlcsc.com/77984.html,1,,,,,,,,
,X2,32.768 kHz,1,XTAL-3.2X1.5,XTAL3215,Low cost SMT crystal,, ¥0.940 , ¥0.94 ,https://item.szlcsc.com/33310.html,1,,,,,,,,
,"U1, U5, U8, U11",TPS63020,4,TPS63020,QFN14-3X4MM,Single Inductor Buck-Boost Converter,TPS63020DSJR, ¥7.000 , ¥28.00 ,https://item.szlcsc.com/16162.html,1,,,,,,,,
,U2,AP2114H-3.3V- 1A,1,AP2114H-3.3V- 1A,SOT223,3.3V Low Dropout Voltage Regulator 1A,AP2114H-3.3TRG1, ¥0.880 , ¥0.88 ,https://item.szlcsc.com/162056.html,1,,,,,,,,
,U3,LM5085,1,LM5085,LM5085,Constant On time PFET Buck Switching Controller,LM5085MY/NOPB, ¥10.550 , ¥10.55 ,https://item.szlcsc.com/80966.html,1,,,,,,,,
,U4,MCP4728-E/UN,1,MCP4728-E/UN,SOP50P490X110-10N,"12Bit I2C DAC, QUAD",MCP4728-E/UN, ¥8.000 , ¥8.00 ,https://item.szlcsc.com/109426.html,1,,,https://detail.tmall.com/item.htm?spm=a230r.1.14.4.64f81c83O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,,,,,
,U6,ATSAMD21G18A-AU,1,ATSAMD21G18A-AU,QFP50P900X900X120-48N,"Cortex-M0+, 256KB FLASH, 32KB SRAM, 48TQFP",ATSAMD21G18A-AU, ¥28.000 , ¥28.00 ,https://item.szlcsc.com/79760.html,1,,,,,,,,
,U7,SPX3819_3.3V,1,VREG_SOT23-5,SOT23-5,Low Noise 3.3V  Voltage Regulator,SPX3819M5-L-3-3/TR , ¥1.090 , ¥1.09 ,https://item.szlcsc.com/9575.html,1,,,,,,,,
,"U9, U10",LMD128D818,2,LMD128D818,ADC128D818,"12-Bit, 8-Channel, ADC System Monitor with Temperature Sensor",ADC128D818CIMTX/NOPB, ¥45.000 , ¥90.00 ,https://item.szlcsc.com/150383.html,1,,,,,,,,
,U12,DRV8871,1,DRV8871,HSOP8,DRV8871 - 3.6A PWM Motor Driver,DRV8871DDAR , ¥8.650 , ¥8.65 ,https://item.szlcsc.com/76991.html,1,,,,,,,,
,"T1, T2, T3",DS18B20,3,DS18B20,TO92,1 Wire Temperature sensor ,DS18B20, ¥4.620 , ¥13.86 ,https://item.szlcsc.com/348632.html,1,,,,,,,,
,D1,MBR120,1,DIODE-SCHOTTKY,SOD-123,Schottky Diode,MBR120LSF, ¥0.200 , ¥0.20 ,https://item.szlcsc.com/142169.html,1,,,,,,,,
,D2,SK104,1,SK104,SK104,Diode,SK104, ¥0.980 , ¥0.98 ,https://item.szlcsc.com/60552.html,1,,,,,,,,
,Q1,PMV48XP,1,PMV48XP,SOT23-R,P-Channel Mosfet,"PMV48XP,215", ¥0.500 , ¥0.50 ,https://item.szlcsc.com/76685.html,1,,,,,,,,
,"Q2, Q3, Q4, Q5",DMN6140L,4,DMN6140L,SOT91P240X110-3N,N-Channel Mosfet,DMN6140L, ¥0.780 , ¥3.12 ,https://item.szlcsc.com/167649.html,1,,,,,,,,
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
